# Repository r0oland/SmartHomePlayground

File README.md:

# SmartHomePlayground

## Install

Make sure to pull submodule!

Run `mamba env create -f environment.yml` to instal HA environment.

`conda activate ha`

`esphome --version`

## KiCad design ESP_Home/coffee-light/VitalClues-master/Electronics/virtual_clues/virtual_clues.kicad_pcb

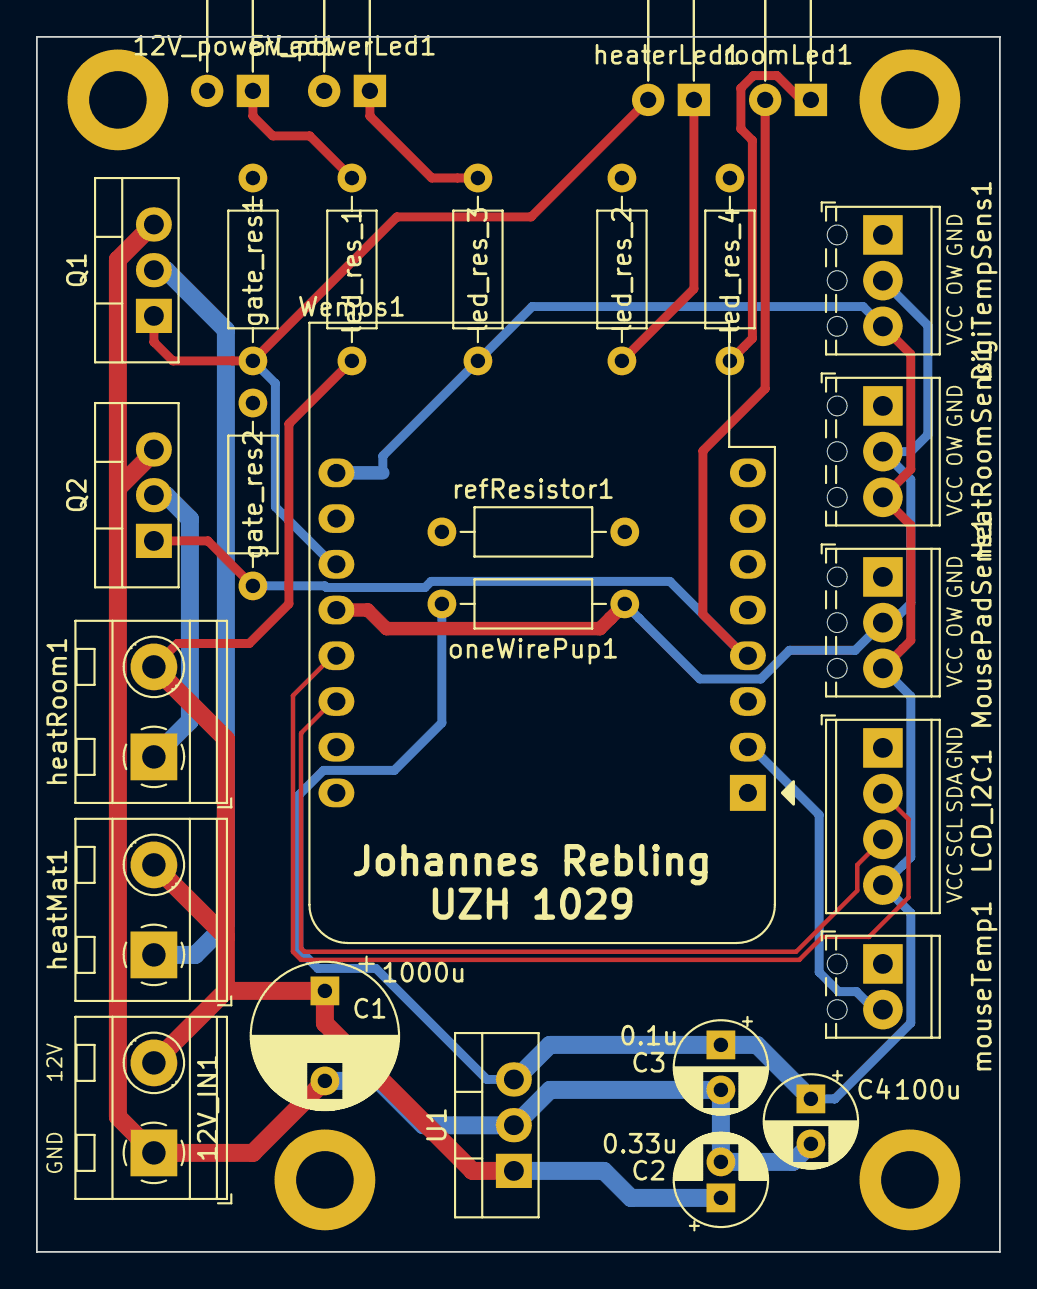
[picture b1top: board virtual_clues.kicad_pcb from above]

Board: 2 copper layers, 53.5 x 67.5 mm, 28 parts (0 on the bottom side), 16 nets.

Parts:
5V_powerLed1: red; LED_D5.0mm_Horizontal_O6.35mm_Z3.0mm
12V_IN1: 12V_IN; TerminalBlock_MetzConnect_Type094_RT03502HBLU_1x02_P5.00mm_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
12V_powerLed1: green; LED_D5.0mm_Horizontal_O6.35mm_Z3.0mm
C1: 1000u; CP_Radial_D8.0mm_P5.00mm
C2: 0.33u; CP_Radial_D5.0mm_P2.00mm
C3: 0.1u; CP_Radial_D5.0mm_P2.50mm
C4: 100u; CP_Radial_D5.0mm_P2.50mm
DigiTempSens1: DigiTempSens2; TerminalBlock_Phoenix_MPT-0,5-3-2.54_1x03_P2.54mm_Horizontal
HeatRoomSens1: DigiTempSens2; TerminalBlock_Phoenix_MPT-0,5-3-2.54_1x03_P2.54mm_Horizontal
LCD_I2C1: LCD_I2C; TerminalBlock_Phoenix_MPT-0,5-4-2.54_1x04_P2.54mm_Horizontal
MousePadSens1: DigiTempSens1; TerminalBlock_Phoenix_MPT-0,5-3-2.54_1x03_P2.54mm_Horizontal
Q1, Q2: IRLB8721PBF; TO-220-3_Vertical
U1: L7805; TO-220-3_Vertical
Wemos1: WeMos_D1_mini; WEMOS_D1_mini_light
gate_res1, gate_res2: 10k; R_Axial_DIN0207_L6.3mm_D2.5mm_P10.16mm_Horizontal
heatMat1: heatMat1; TerminalBlock_MetzConnect_Type094_RT03502HBLU_1x02_P5.00mm_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
heatRoom1: heatMat1; TerminalBlock_MetzConnect_Type094_RT03502HBLU_1x02_P5.00mm_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
heaterLed1: heaterLed; LED_D5.0mm_Horizontal_O6.35mm_Z3.0mm
led_res_1: 560; R_Axial_DIN0207_L6.3mm_D2.5mm_P10.16mm_Horizontal
led_res_2, led_res_3, led_res_4: 150; R_Axial_DIN0207_L6.3mm_D2.5mm_P10.16mm_Horizontal
mouseTemp1: mouseTemp; TerminalBlock_Phoenix_MPT-0,5-2-2.54_1x02_P2.54mm_Horizontal
oneWirePup1: 4.7k; R_Axial_DIN0207_L6.3mm_D2.5mm_P10.16mm_Horizontal
refResistor1: 10k; R_Axial_DIN0207_L6.3mm_D2.5mm_P10.16mm_Horizontal
roomLed1: heaterLed; LED_D5.0mm_Horizontal_O6.35mm_Z3.0mm

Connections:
+3V3: Wemos1.8, refResistor1.1
+12V: 12V_IN1.2, C1.1, C2.1, U1.1, heatMat1.2, heatRoom1.2, led_res_1.1
AnTempSens: Wemos1.2, mouseTemp1.2, refResistor1.2
GND: 5V_powerLed1.2, 12V_IN1.1, 12V_powerLed1.2, C1.2, C2.2, C3.2, C4.2, DigiTempSens1.1, HeatRoomSens1.1, LCD_I2C1.1, MousePadSens1.1, Q1.3, Q2.3, U1.2, Wemos1.1, Wemos1.10, gate_res1.2, gate_res2.2, led_res_2.2, led_res_4.2, mouseTemp1.1
HeatPadCtr: Q1.1, Wemos1.11, gate_res1.1, heaterLed1.2
HeatRoom: Q2.1, Wemos1.4, gate_res2.1, roomLed1.2
unnamed: 5V_powerLed1.1, led_res_3.2
unnamed: 12V_powerLed1.1, led_res_1.2
unnamed: Q1.2, heatMat1.1
unnamed: Q2.2, heatRoom1.1
unnamed: heaterLed1.1, led_res_2.1
unnamed: led_res_4.1, roomLed1.1
OneWireBus: DigiTempSens1.2, HeatRoomSens1.2, MousePadSens1.2, Wemos1.12, oneWirePup1.2
SCL: LCD_I2C1.3, Wemos1.14
SDA: LCD_I2C1.2, Wemos1.13
VCC: C3.1, C4.1, DigiTempSens1.3, HeatRoomSens1.3, LCD_I2C1.4, MousePadSens1.3, U1.3, Wemos1.9, led_res_3.1, oneWirePup1.1

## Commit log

2022-09-27 - adding secrets submodules - first super simple example working to get my started again...
2022-09-27 - adding display, playing with analog out
2022-09-27 - submod update
2022-10-03 - adding D1 mini desk jockey - terrarium updates with lights and pyscript automations
2022-10-24 - getting analog gauges gauging
2023-11-26 - getting new szenarium D1 mini code with rugged temperature sensor up and running
2024-10-26 Getting up and running with ESPHome again
2024-11-23 Working on coffee lights
2024-11-27 Adding vital clues kicad files from yesteryear...
2024-11-27 Adding partitions and effects to ESP Home Coffee Light
2024-12-03 Adding basic bedroom light
2025-01-26 Coffee-Lights for Michi
